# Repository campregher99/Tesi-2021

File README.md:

# Tesi-2021
progetto di tesi SCARA repository personale di backup

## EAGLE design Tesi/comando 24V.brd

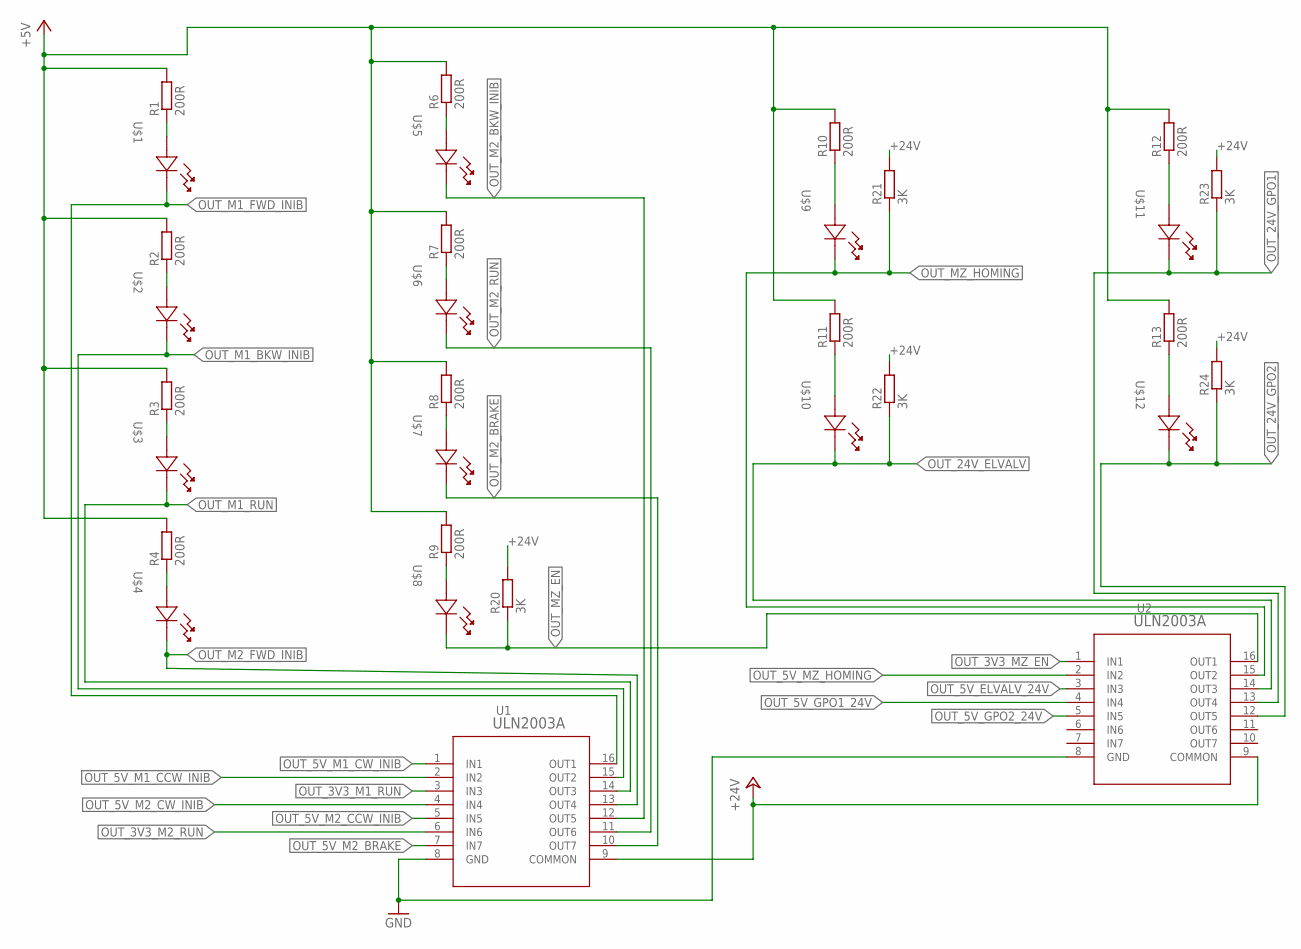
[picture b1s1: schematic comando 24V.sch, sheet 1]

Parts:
R1, R2, R3, R4, R6, R7, R8, R9, R10, R11, R12, R13: 200R; 0207/10
R20, R21, R22, R23, R24: 3K; 0207/10
U1, U2: ULN2003A; DIP-16_STM
U$1, U$2, U$3, U$4, U$5, U$6, U$7, U$8, U$9, U$10, U$11, U$12: LED_TONDO

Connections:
+5V: R1.2, R2.2, R3.2, R4.2, R6.2, R7.2, R8.2, R9.2, R10.2, R11.2, R12.2, R13.2; also elsewhere on the board
+24V: R20.2, R21.2, R22.2, R23.2, R24.2, U1.9 (COMMON), U2.9 (COMMON); also elsewhere on the board
GND: U1.8 (GND), U2.8 (GND); also elsewhere on the board
unnamed: R1.1, U$1.2
unnamed: R2.1, U$2.2
unnamed: R3.1, U$3.2
unnamed: R4.1, U$4.2
unnamed: R6.1, U$5.2
unnamed: R7.1, U$6.2
unnamed: R8.1, U$7.2
unnamed: R9.1, U$8.2
unnamed: R10.1, U$9.2
unnamed: R11.1, U$10.2
unnamed: R12.1, U$11.2
unnamed: R13.1, U$12.2
OUT_3V3_M1_RUN: U1.3 (IN3); also elsewhere on the board
OUT_3V3_M2_RUN: U1.6 (IN6); also elsewhere on the board
OUT_3V3_MZ_EN: U2.1 (IN1); also elsewhere on the board
OUT_5V_ELVALV_24V: U2.3 (IN3); also elsewhere on the board
OUT_5V_GPO1_24V: U2.4 (IN4); also elsewhere on the board
OUT_5V_GPO2_24V: U2.5 (IN5); also elsewhere on the board
OUT_5V_M1_CCW_INIB: U1.2 (IN2); also elsewhere on the board
OUT_5V_M1_CW_INIB: U1.1 (IN1); also elsewhere on the board
OUT_5V_M2_BRAKE: U1.7 (IN7); also elsewhere on the board
OUT_5V_M2_CCW_INIB: U1.5 (IN5); also elsewhere on the board
OUT_5V_M2_CW_INIB: U1.4 (IN4); also elsewhere on the board
OUT_5V_MZ_HOMING: U2.2 (IN2); also elsewhere on the board
OUT_24V_ELVALV: R22.1, U2.14 (OUT3), U$10.1; also elsewhere on the board
OUT_24V_GPO1: R23.1, U2.13 (OUT4), U$11.1; also elsewhere on the board
OUT_24V_GPO2: R24.1, U2.12 (OUT5), U$12.1; also elsewhere on the board
OUT_M1_BKW_INIB: U1.15 (OUT2), U$2.1; also elsewhere on the board
OUT_M1_FWD_INIB: U1.16 (OUT1), U$1.1; also elsewhere on the board
OUT_M1_RUN: U1.14 (OUT3), U$3.1; also elsewhere on the board
OUT_M2_BKW_INIB: U1.12 (OUT5), U$5.1; also elsewhere on the board
OUT_M2_BRAKE: U1.10 (OUT7), U$7.1; also elsewhere on the board
OUT_M2_FWD_INIB: U1.13 (OUT4), U$4.1; also elsewhere on the board
OUT_M2_RUN: U1.11 (OUT6), U$6.1; also elsewhere on the board
OUT_MZ_EN: R20.1, U2.16 (OUT1), U$8.1; also elsewhere on the board
OUT_MZ_HOMING: R21.1, U2.15 (OUT2), U$9.1; also elsewhere on the board

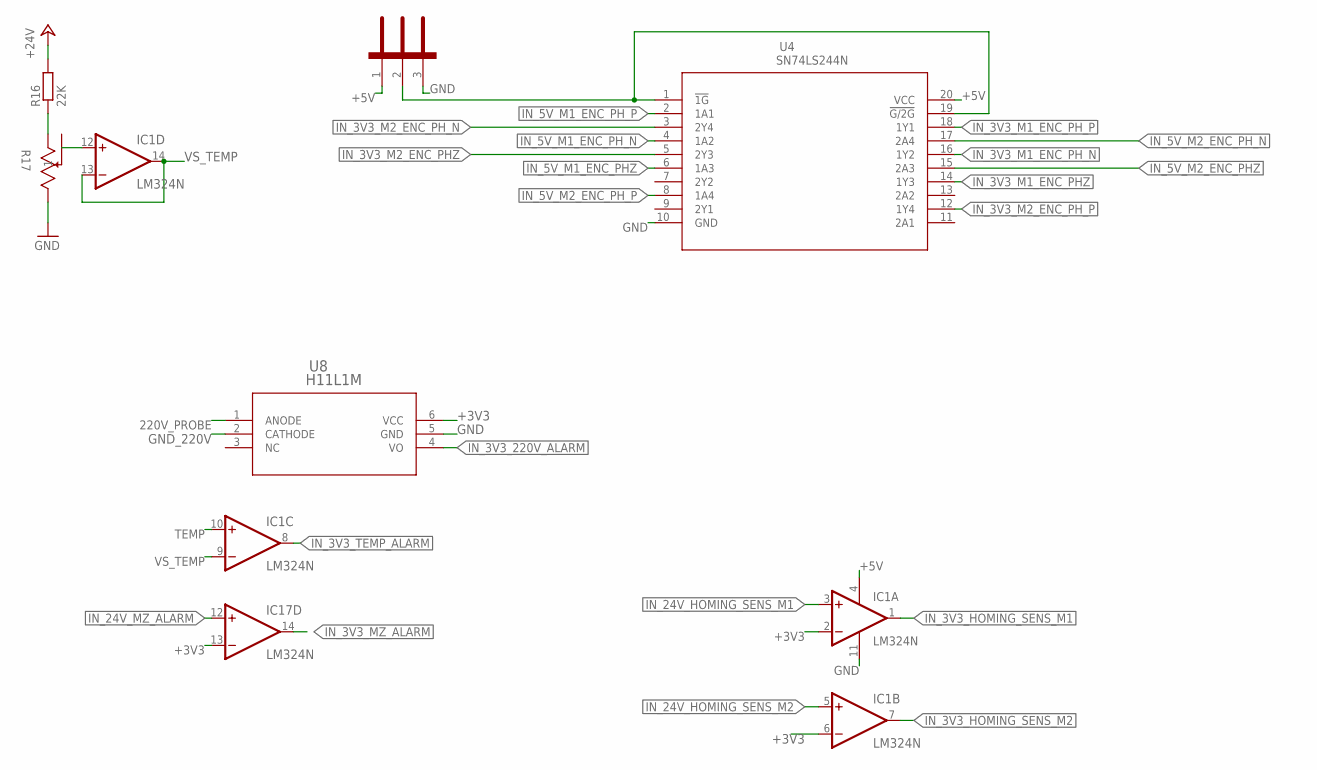
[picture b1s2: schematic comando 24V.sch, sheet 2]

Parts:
EN_IN_ENC: STRIP_3
IC1, IC17: LM324N; DIL14
R16: 22K; 0207/10
R17: TEMP_ADJ; RES3_64W_TTE
U4: SN74LS244N; N20
U8: H11L1M; PDIP6-646BX_ONS

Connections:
220V_PROBE: U8.1 (ANODE); also elsewhere on the board
+3V3: IC1.2 (-IN), IC1.6 (-IN), IC17.13 (-IN), U8.6 (VCC); also elsewhere on the board
+5V: EN_IN_ENC.1, IC1.4 (V+), U4.20 (VCC); also elsewhere on the board
+24V: R16.2; also elsewhere on the board
GND: EN_IN_ENC.3, IC1.11 (V-), R17.3, U4.10 (GND), U8.5 (GND); also elsewhere on the board
GND_220V: U8.2 (CATHODE); also elsewhere on the board
IN_3V3_220V_ALARM: U8.4 (VO); also elsewhere on the board
IN_3V3_HOMING_SENS_M1: IC1.1 (OUT); also elsewhere on the board
IN_3V3_HOMING_SENS_M2: IC1.7 (OUT); also elsewhere on the board
IN_3V3_M1_ENC_PHZ: U4.14 (1Y3); also elsewhere on the board
IN_3V3_M1_ENC_PH_N: U4.16 (1Y2); also elsewhere on the board
IN_3V3_M1_ENC_PH_P: U4.18 (1Y1); also elsewhere on the board
IN_3V3_M2_ENC_PHZ: U4.5 (2Y3); also elsewhere on the board
IN_3V3_M2_ENC_PH_N: U4.3 (2Y4); also elsewhere on the board
IN_3V3_M2_ENC_PH_P: U4.12 (1Y4); also elsewhere on the board
IN_3V3_MZ_ALARM: IC17.14 (OUT); also elsewhere on the board
IN_3V3_TEMP_ALARM: IC1.8 (OUT); also elsewhere on the board
IN_5V_M1_ENC_PHZ: U4.6 (1A3); also elsewhere on the board
IN_5V_M1_ENC_PH_N: U4.4 (1A2); also elsewhere on the board
IN_5V_M1_ENC_PH_P: U4.2 (1A1); also elsewhere on the board
IN_5V_M2_ENC_PHZ: U4.15 (2A3); also elsewhere on the board
IN_5V_M2_ENC_PH_N: U4.17 (2A4); also elsewhere on the board
IN_5V_M2_ENC_PH_P: U4.8 (1A4); also elsewhere on the board
IN_24V_HOMING_SENS_M1: IC1.3 (+IN); also elsewhere on the board
IN_24V_HOMING_SENS_M2: IC1.5 (+IN); also elsewhere on the board
IN_24V_MZ_ALARM: IC17.12 (+IN); also elsewhere on the board
unnamed: R16.1, R17.1
unnamed: IC1.12 (+IN), R17.2
unnamed: EN_IN_ENC.2, U4.1 (!1G), U4.19 (!G/2G)
TEMP: IC1.10 (+IN); also elsewhere on the board
VS_TEMP: IC1.9 (-IN), IC1.13 (-IN), IC1.14 (OUT)

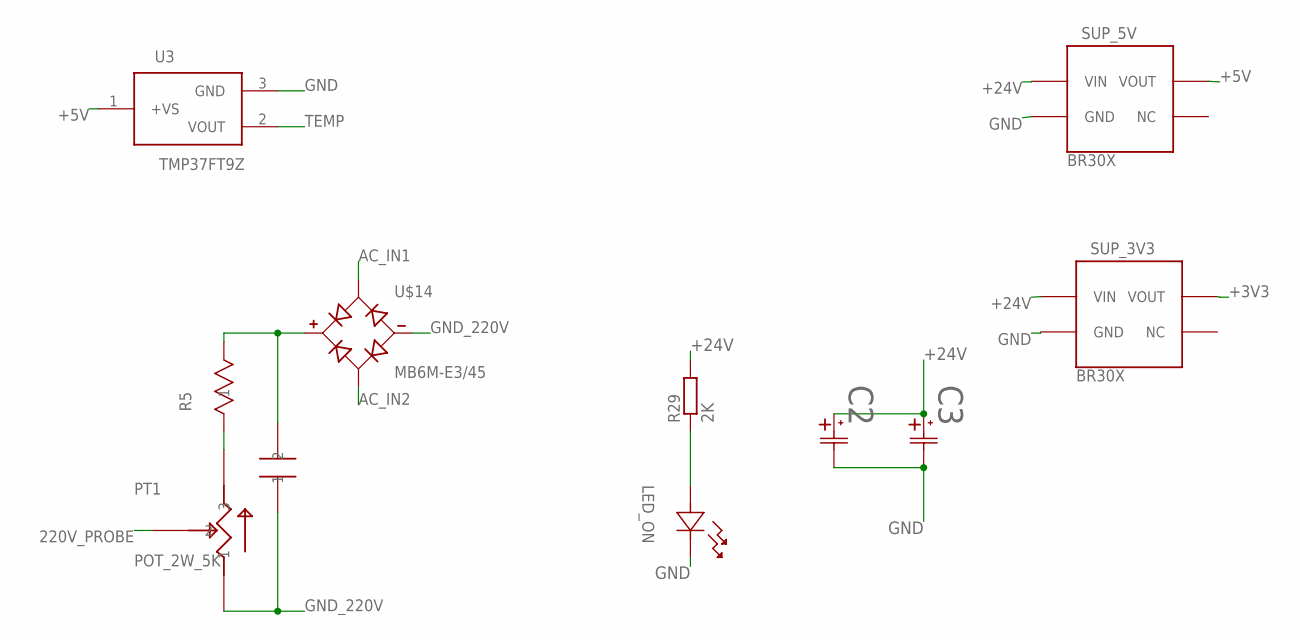
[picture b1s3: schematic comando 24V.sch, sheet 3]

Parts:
C2: QYX1H102JTP3TA; CAP_QYX_2P5X5X8P5_NCH
C3: UBY2A301MHL; CAP_UBY_12P5X31P5_NCH
PT1: POT_2W_5K
R5: OY104KE; RES_OY_OHM
R29: 2K; 0207/10
SUP_3V3, SUP_5V: BR30X
U3: TMP37FT9Z; T_3_ADI
U$13: C0U12F
U$14: MB6M-E3/45; DIP508W58P254L483H270Q4
U$15: LED_ON; LED_TONDO

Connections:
220V_PROBE: PT1.2; also elsewhere on the board
+3V3: SUP_3V3.VOUT; also elsewhere on the board
+5V: SUP_5V.VOUT, U3.1 (+VS); also elsewhere on the board
+24V: C2.1, C3.1, R29.2, SUP_3V3.VIN, SUP_5V.VIN; also elsewhere on the board
AC_IN1: U$14.3 (AC1); also elsewhere on the board
AC_IN2: U$14.4 (AC2); also elsewhere on the board
GND: C2.2, C3.2, SUP_3V3.GND, SUP_5V.GND, U3.3 (GND), U$15.1; also elsewhere on the board
GND_220V: PT1.1, U$13.P$2 (2), U$14.2 (-); also elsewhere on the board
unnamed: R5.2, U$13.P$1 (1), U$14.1 (+)
unnamed: R29.1, U$15.2
unnamed: PT1.3, R5.1
TEMP: U3.2 (VOUT); also elsewhere on the board

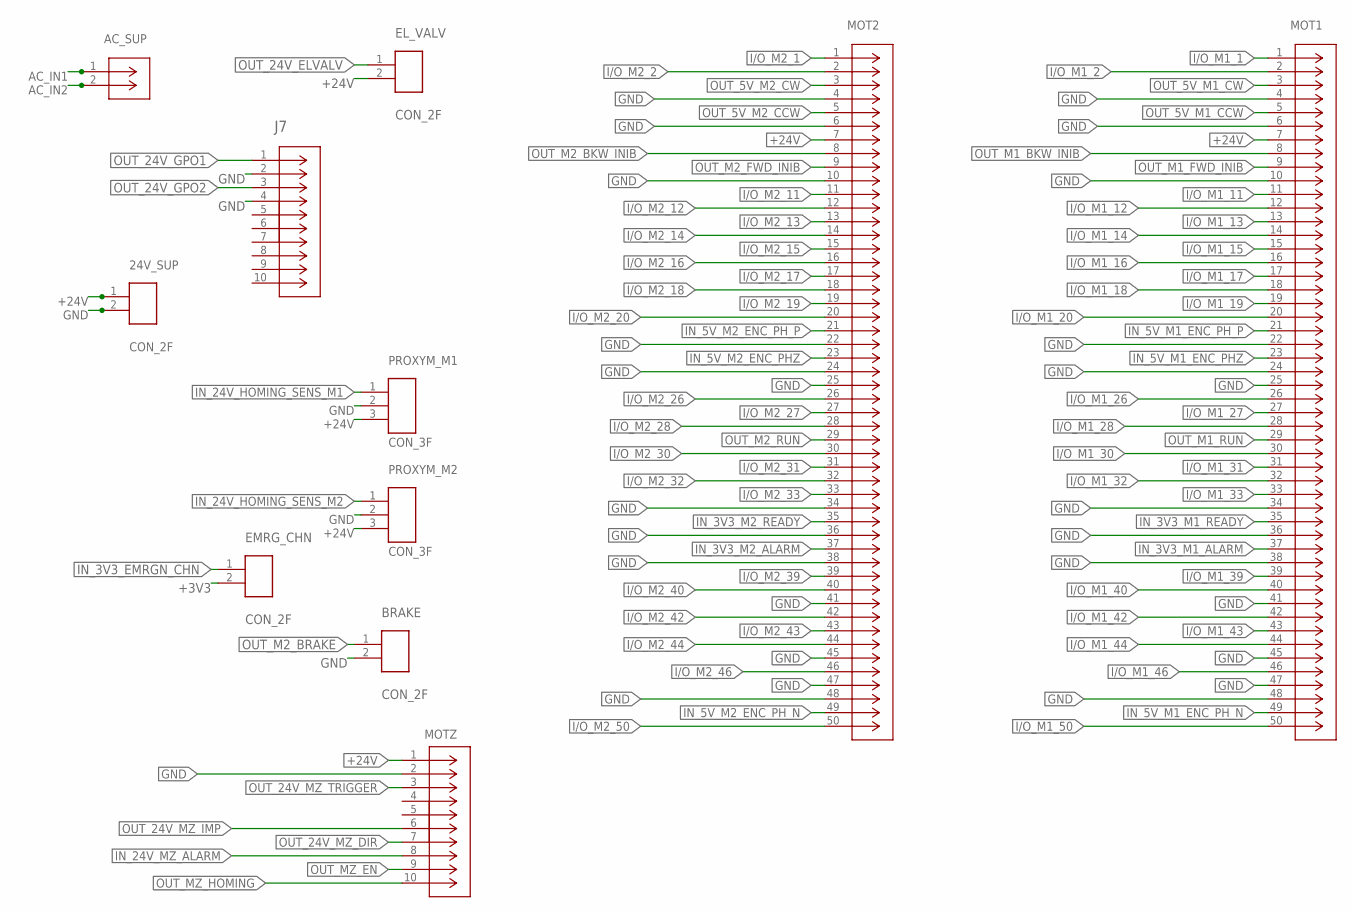
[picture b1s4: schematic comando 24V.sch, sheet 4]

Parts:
24V_SUP: CON_2F
AC_SUP: B2B-XH-A(LF)(SN); CONN_B2B-XH-A(LF)(SN)_JST
BRAKE: CON_2F
EL_VALV: CON_2F
EMRG_CHN: CON_2F
J7: 61201021621; CONN_61201021621_WRE
MOT1, MOT2: SBH11-PBPC-D25-ST-BK; CONN_SBH11-PBPC-D25-ST-BK_SUL
MOTZ: 61201021621; CONN_61201021621_WRE
PROXYM_M1, PROXYM_M2: CON_3F

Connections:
+3V3: EMRG_CHN.2; also elsewhere on the board
+24V: 24V_SUP.1, EL_VALV.2, MOT1.7, MOT2.7, MOTZ.1, PROXYM_M1.3, PROXYM_M2.3; also elsewhere on the board
AC_IN1: AC_SUP.1; also elsewhere on the board
AC_IN2: AC_SUP.2; also elsewhere on the board
GND: 24V_SUP.2, BRAKE.2, J7.2, J7.4, MOT1.4, MOT1.6, MOT1.10, MOT1.22, MOT1.24, MOT1.25, MOT1.34, MOT1.36, MOT1.38, MOT1.41, MOT1.45, MOT1.47, MOT1.48, MOT2.4, MOT2.6, MOT2.10, MOT2.22, MOT2.24, MOT2.25, MOT2.34, MOT2.36, MOT2.38, MOT2.41, MOT2.45, MOT2.47, MOT2.48, MOTZ.2, PROXYM_M1.2, PROXYM_M2.2; also elsewhere on the board
I/O_M1_1: MOT1.1; also elsewhere on the board
I/O_M1_2: MOT1.2; also elsewhere on the board
I/O_M1_11: MOT1.11; also elsewhere on the board
I/O_M1_12: MOT1.12; also elsewhere on the board
I/O_M1_13: MOT1.13; also elsewhere on the board
I/O_M1_14: MOT1.14; also elsewhere on the board
I/O_M1_15: MOT1.15; also elsewhere on the board
I/O_M1_16: MOT1.16; also elsewhere on the board
I/O_M1_17: MOT1.17; also elsewhere on the board
I/O_M1_18: MOT1.18; also elsewhere on the board
I/O_M1_19: MOT1.19; also elsewhere on the board
I/O_M1_20: MOT1.20; also elsewhere on the board
I/O_M1_26: MOT1.26; also elsewhere on the board
I/O_M1_27: MOT1.27; also elsewhere on the board
I/O_M1_28: MOT1.28; also elsewhere on the board
I/O_M1_30: MOT1.30; also elsewhere on the board
I/O_M1_31: MOT1.31; also elsewhere on the board
I/O_M1_32: MOT1.32; also elsewhere on the board
I/O_M1_33: MOT1.33; also elsewhere on the board
I/O_M1_39: MOT1.39; also elsewhere on the board
I/O_M1_40: MOT1.40; also elsewhere on the board
I/O_M1_42: MOT1.42; also elsewhere on the board
I/O_M1_43: MOT1.43; also elsewhere on the board
I/O_M1_44: MOT1.44; also elsewhere on the board
I/O_M1_46: MOT1.46; also elsewhere on the board
I/O_M1_50: MOT1.50; also elsewhere on the board
I/O_M2_1: MOT2.1; also elsewhere on the board
I/O_M2_2: MOT2.2; also elsewhere on the board
I/O_M2_11: MOT2.11; also elsewhere on the board
I/O_M2_12: MOT2.12; also elsewhere on the board
I/O_M2_13: MOT2.13; also elsewhere on the board
I/O_M2_14: MOT2.14; also elsewhere on the board
I/O_M2_15: MOT2.15; also elsewhere on the board
I/O_M2_16: MOT2.16; also elsewhere on the board
I/O_M2_17: MOT2.17; also elsewhere on the board
I/O_M2_18: MOT2.18; also elsewhere on the board
I/O_M2_19: MOT2.19; also elsewhere on the board
I/O_M2_20: MOT2.20; also elsewhere on the board
I/O_M2_26: MOT2.26; also elsewhere on the board
I/O_M2_27: MOT2.27; also elsewhere on the board
I/O_M2_28: MOT2.28; also elsewhere on the board
I/O_M2_30: MOT2.30; also elsewhere on the board
I/O_M2_31: MOT2.31; also elsewhere on the board
I/O_M2_32: MOT2.32; also elsewhere on the board
I/O_M2_33: MOT2.33; also elsewhere on the board
I/O_M2_39: MOT2.39; also elsewhere on the board
I/O_M2_40: MOT2.40; also elsewhere on the board
I/O_M2_42: MOT2.42; also elsewhere on the board
I/O_M2_43: MOT2.43; also elsewhere on the board
I/O_M2_44: MOT2.44; also elsewhere on the board
I/O_M2_46: MOT2.46; also elsewhere on the board
I/O_M2_50: MOT2.50; also elsewhere on the board
IN_3V3_EMRGN_CHN: EMRG_CHN.1; also elsewhere on the board
IN_3V3_M1_ALARM: MOT1.37; also elsewhere on the board
IN_3V3_M1_READY: MOT1.35; also elsewhere on the board
IN_3V3_M2_ALARM: MOT2.37; also elsewhere on the board
IN_3V3_M2_READY: MOT2.35; also elsewhere on the board
IN_5V_M1_ENC_PHZ: MOT1.23; also elsewhere on the board
IN_5V_M1_ENC_PH_N: MOT1.49; also elsewhere on the board
IN_5V_M1_ENC_PH_P: MOT1.21; also elsewhere on the board
IN_5V_M2_ENC_PHZ: MOT2.23; also elsewhere on the board
IN_5V_M2_ENC_PH_N: MOT2.49; also elsewhere on the board
IN_5V_M2_ENC_PH_P: MOT2.21; also elsewhere on the board
IN_24V_HOMING_SENS_M1: PROXYM_M1.1; also elsewhere on the board
IN_24V_HOMING_SENS_M2: PROXYM_M2.1; also elsewhere on the board
IN_24V_MZ_ALARM: MOTZ.8; also elsewhere on the board
OUT_5V_M1_CCW: MOT1.5; also elsewhere on the board
OUT_5V_M1_CW: MOT1.3; also elsewhere on the board
OUT_5V_M2_CCW: MOT2.5; also elsewhere on the board
OUT_5V_M2_CW: MOT2.3; also elsewhere on the board
OUT_24V_ELVALV: EL_VALV.1; also elsewhere on the board
OUT_24V_GPO1: J7.1; also elsewhere on the board
OUT_24V_GPO2: J7.3; also elsewhere on the board
OUT_24V_MZ_DIR: MOTZ.7; also elsewhere on the board
OUT_24V_MZ_IMP: MOTZ.6; also elsewhere on the board
OUT_24V_MZ_TRIGGER: MOTZ.3; also elsewhere on the board
OUT_M1_BKW_INIB: MOT1.8; also elsewhere on the board
OUT_M1_FWD_INIB: MOT1.9; also elsewhere on the board
OUT_M1_RUN: MOT1.29; also elsewhere on the board
OUT_M2_BKW_INIB: MOT2.8; also elsewhere on the board
OUT_M2_BRAKE: BRAKE.1; also elsewhere on the board
OUT_M2_FWD_INIB: MOT2.9; also elsewhere on the board
OUT_M2_RUN: MOT2.29; also elsewhere on the board
OUT_MZ_EN: MOTZ.9; also elsewhere on the board
OUT_MZ_HOMING: MOTZ.10; also elsewhere on the board

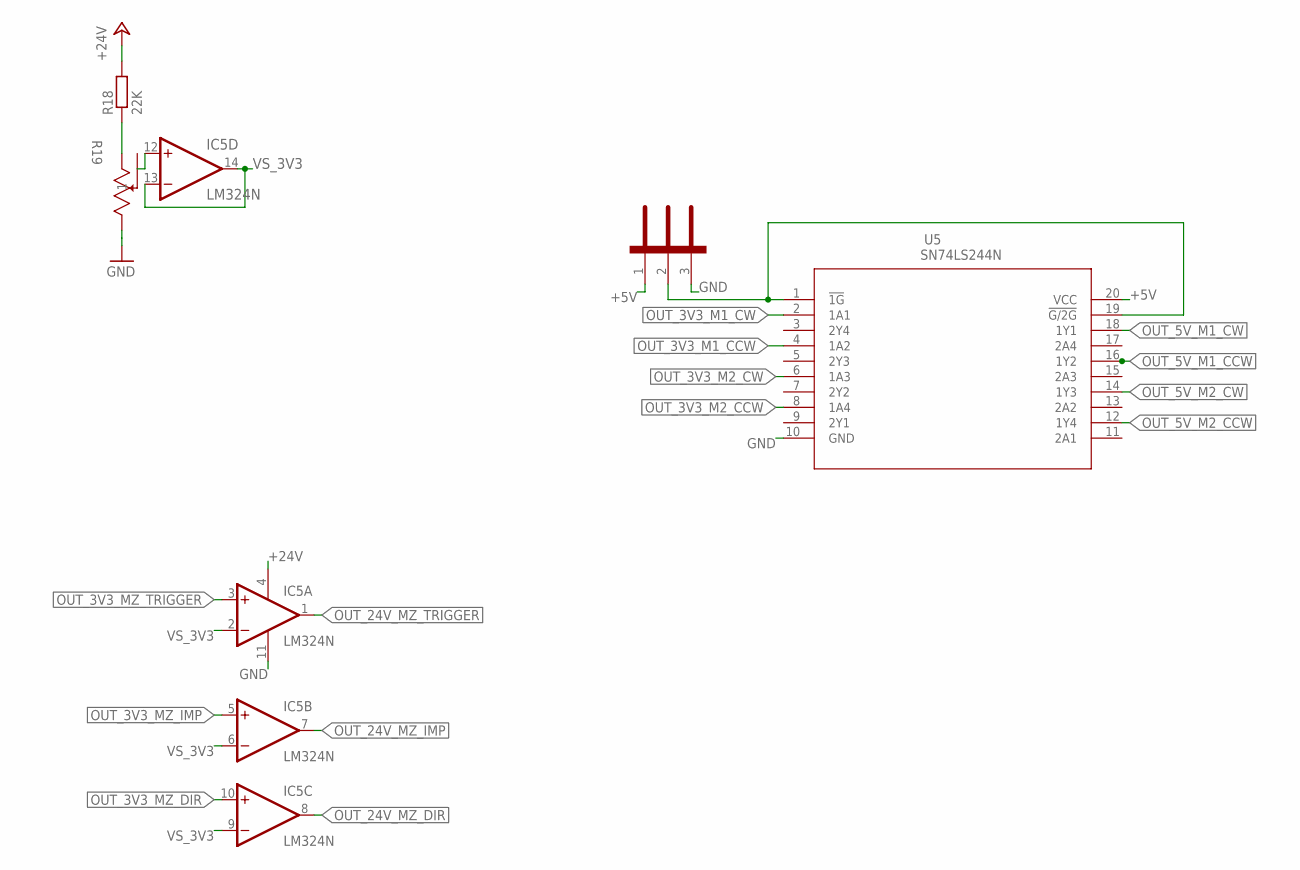
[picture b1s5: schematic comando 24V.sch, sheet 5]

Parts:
EN_OUT_MOT: STRIP_3
IC5: LM324N; DIL14
R18: 22K; 0207/10
R19: VS_3V3_ADJ; RES3_64W_TTE
U5: SN74LS244N; N20

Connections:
+5V: EN_OUT_MOT.1, U5.20 (VCC); also elsewhere on the board
+24V: IC5.4 (V+), R18.2; also elsewhere on the board
GND: EN_OUT_MOT.3, IC5.11 (V-), R19.3, U5.10 (GND); also elsewhere on the board
unnamed: EN_OUT_MOT.2, U5.1 (!1G), U5.19 (!G/2G)
unnamed: IC5.12 (+IN), R19.2
unnamed: R18.1, R19.1
OUT_3V3_M1_CCW: U5.4 (1A2); also elsewhere on the board
OUT_3V3_M1_CW: U5.2 (1A1); also elsewhere on the board
OUT_3V3_M2_CCW: U5.8 (1A4); also elsewhere on the board
OUT_3V3_M2_CW: U5.6 (1A3); also elsewhere on the board
OUT_3V3_MZ_DIR: IC5.10 (+IN); also elsewhere on the board
OUT_3V3_MZ_IMP: IC5.5 (+IN); also elsewhere on the board
OUT_3V3_MZ_TRIGGER: IC5.3 (+IN); also elsewhere on the board
OUT_5V_M1_CCW: U5.16 (1Y2); also elsewhere on the board
OUT_5V_M1_CW: U5.18 (1Y1); also elsewhere on the board
OUT_5V_M2_CCW: U5.12 (1Y4); also elsewhere on the board
OUT_5V_M2_CW: U5.14 (1Y3); also elsewhere on the board
OUT_24V_MZ_DIR: IC5.8 (OUT); also elsewhere on the board
OUT_24V_MZ_IMP: IC5.7 (OUT); also elsewhere on the board
OUT_24V_MZ_TRIGGER: IC5.1 (OUT); also elsewhere on the board
VS_3V3: IC5.2 (-IN), IC5.6 (-IN), IC5.9 (-IN), IC5.13 (-IN), IC5.14 (OUT)

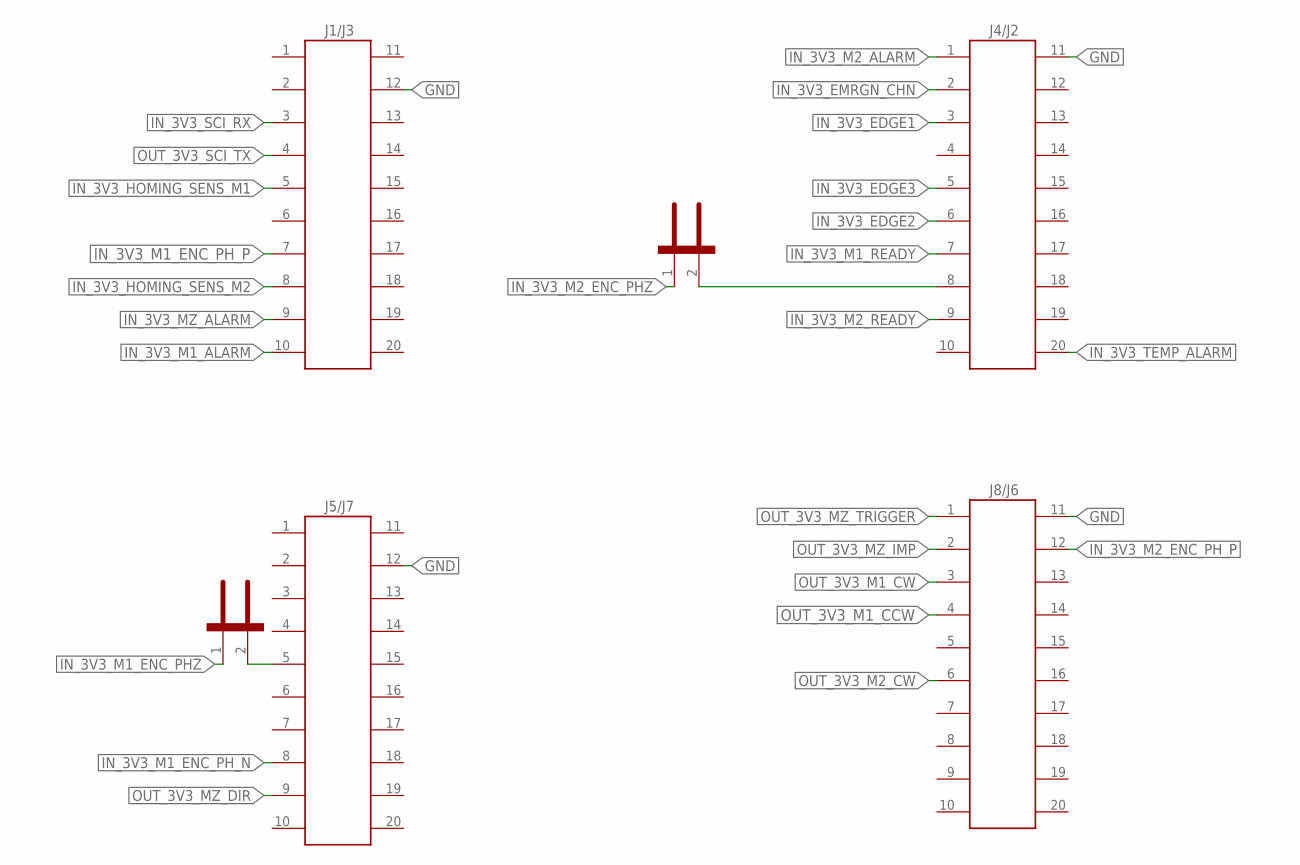
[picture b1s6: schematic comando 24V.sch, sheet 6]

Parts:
EN_M1_ENC_PHZ, EN_M2_ENC_PHZ: STRIP_2
J1/J3, J4/J2, J5/J7, J8/J6: 61202021621

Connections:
GND: J1/J3.12 (4), J4/J2.11 (2), J5/J7.12 (4), J8/J6.11 (2); also elsewhere on the board
IN_3V3_EDGE1: J4/J2.3 (5); also elsewhere on the board
IN_3V3_EDGE2: J4/J2.6 (11); also elsewhere on the board
IN_3V3_EDGE3: J4/J2.5 (9); also elsewhere on the board
IN_3V3_EMRGN_CHN: J4/J2.2 (3); also elsewhere on the board
IN_3V3_HOMING_SENS_M1: J1/J3.5 (9); also elsewhere on the board
IN_3V3_HOMING_SENS_M2: J1/J3.8 (15); also elsewhere on the board
IN_3V3_M1_ALARM: J1/J3.10 (19); also elsewhere on the board
IN_3V3_M1_ENC_PHZ: EN_M1_ENC_PHZ.1; also elsewhere on the board
IN_3V3_M1_ENC_PH_N: J5/J7.8 (15); also elsewhere on the board
IN_3V3_M1_ENC_PH_P: J1/J3.7 (13); also elsewhere on the board
IN_3V3_M1_READY: J4/J2.7 (13); also elsewhere on the board
IN_3V3_M2_ALARM: J4/J2.1; also elsewhere on the board
IN_3V3_M2_ENC_PHZ: EN_M2_ENC_PHZ.1; also elsewhere on the board
IN_3V3_M2_ENC_PH_P: J8/J6.12 (4); also elsewhere on the board
IN_3V3_M2_READY: J4/J2.9 (17); also elsewhere on the board
IN_3V3_MZ_ALARM: J1/J3.9 (17); also elsewhere on the board
IN_3V3_SCI_RX: J1/J3.3 (5); also elsewhere on the board
IN_3V3_TEMP_ALARM: J4/J2.20; also elsewhere on the board
unnamed: EN_M2_ENC_PHZ.2, J4/J2.8 (15)
unnamed: EN_M1_ENC_PHZ.2, J5/J7.5 (9)
OUT_3V3_M1_CCW: J8/J6.4 (7); also elsewhere on the board
OUT_3V3_M1_CW: J8/J6.3 (5); also elsewhere on the board
OUT_3V3_M2_CW: J8/J6.6 (11); also elsewhere on the board
OUT_3V3_MZ_DIR: J5/J7.9 (17); also elsewhere on the board
OUT_3V3_MZ_IMP: J8/J6.2 (3); also elsewhere on the board
OUT_3V3_MZ_TRIGGER: J8/J6.1; also elsewhere on the board
OUT_3V3_SCI_TX: J1/J3.4 (7); also elsewhere on the board

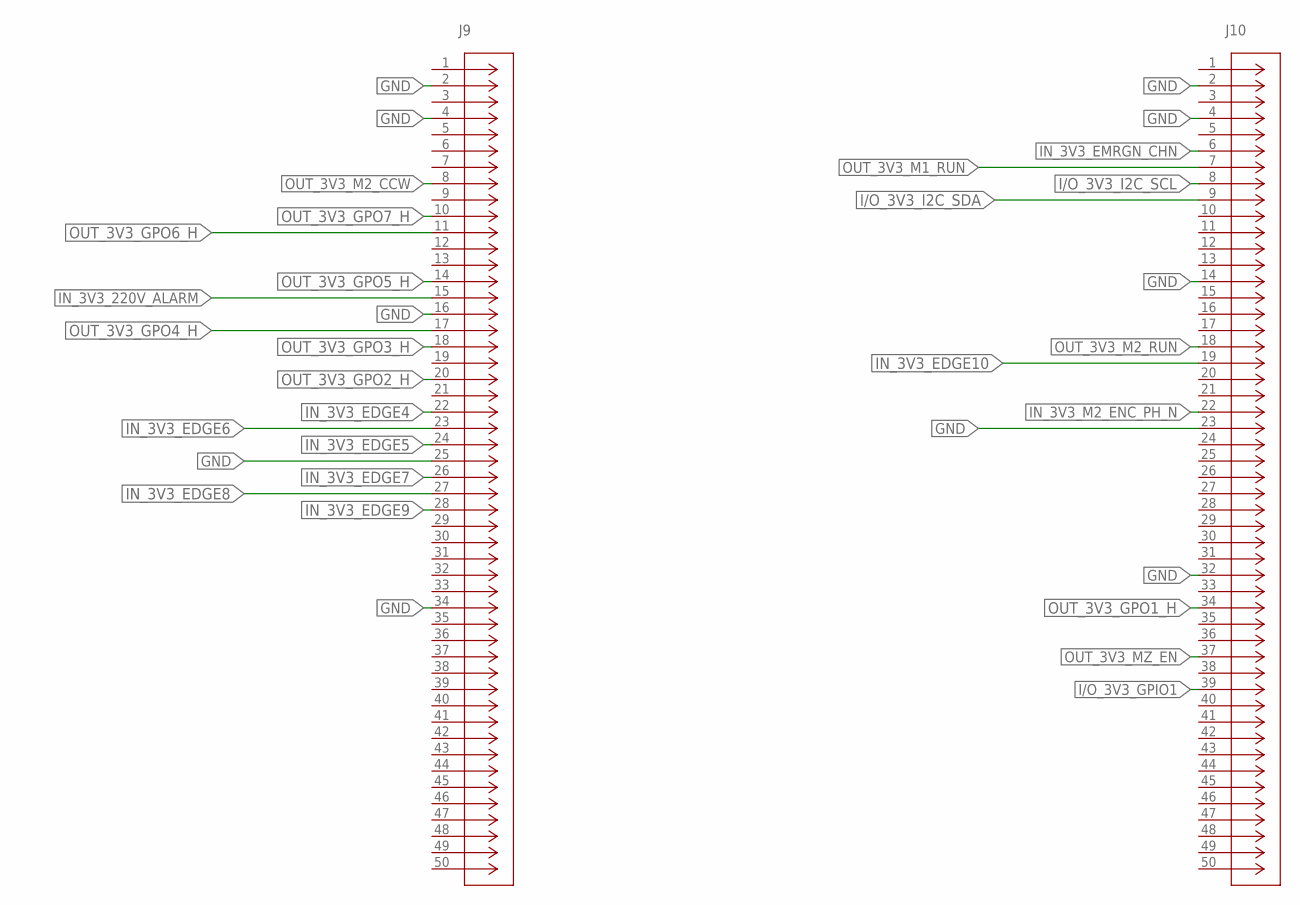
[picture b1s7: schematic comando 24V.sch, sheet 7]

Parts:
J9, J10: SBH11-PBPC-D25-ST-BK; CONN_SBH11-PBPC-D25-ST-BK_SUL

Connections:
GND: J9.2, J9.4, J9.16, J9.25, J9.34, J10.2, J10.4, J10.14, J10.23, J10.32; also elsewhere on the board
I/O_3V3_GPIO1: J10.39; also elsewhere on the board
I/O_3V3_I2C_SCL: J10.8; also elsewhere on the board
I/O_3V3_I2C_SDA: J10.9; also elsewhere on the board
IN_3V3_220V_ALARM: J9.15; also elsewhere on the board
IN_3V3_EDGE4: J9.22; also elsewhere on the board
IN_3V3_EDGE5: J9.24; also elsewhere on the board
IN_3V3_EDGE6: J9.23; also elsewhere on the board
IN_3V3_EDGE7: J9.26; also elsewhere on the board
IN_3V3_EDGE8: J9.27; also elsewhere on the board
IN_3V3_EDGE9: J9.28; also elsewhere on the board
IN_3V3_EDGE10: J10.19; also elsewhere on the board
IN_3V3_EMRGN_CHN: J10.6; also elsewhere on the board
IN_3V3_M2_ENC_PH_N: J10.22; also elsewhere on the board
OUT_3V3_GPO1_H: J10.34; also elsewhere on the board
OUT_3V3_GPO2_H: J9.20; also elsewhere on the board
OUT_3V3_GPO3_H: J9.18; also elsewhere on the board
OUT_3V3_GPO4_H: J9.17; also elsewhere on the board
OUT_3V3_GPO5_H: J9.14; also elsewhere on the board
OUT_3V3_GPO6_H: J9.11; also elsewhere on the board
OUT_3V3_GPO7_H: J9.10; also elsewhere on the board
OUT_3V3_M1_RUN: J10.7; also elsewhere on the board
OUT_3V3_M2_CCW: J9.8; also elsewhere on the board
OUT_3V3_M2_RUN: J10.18; also elsewhere on the board
OUT_3V3_MZ_EN: J10.37; also elsewhere on the board

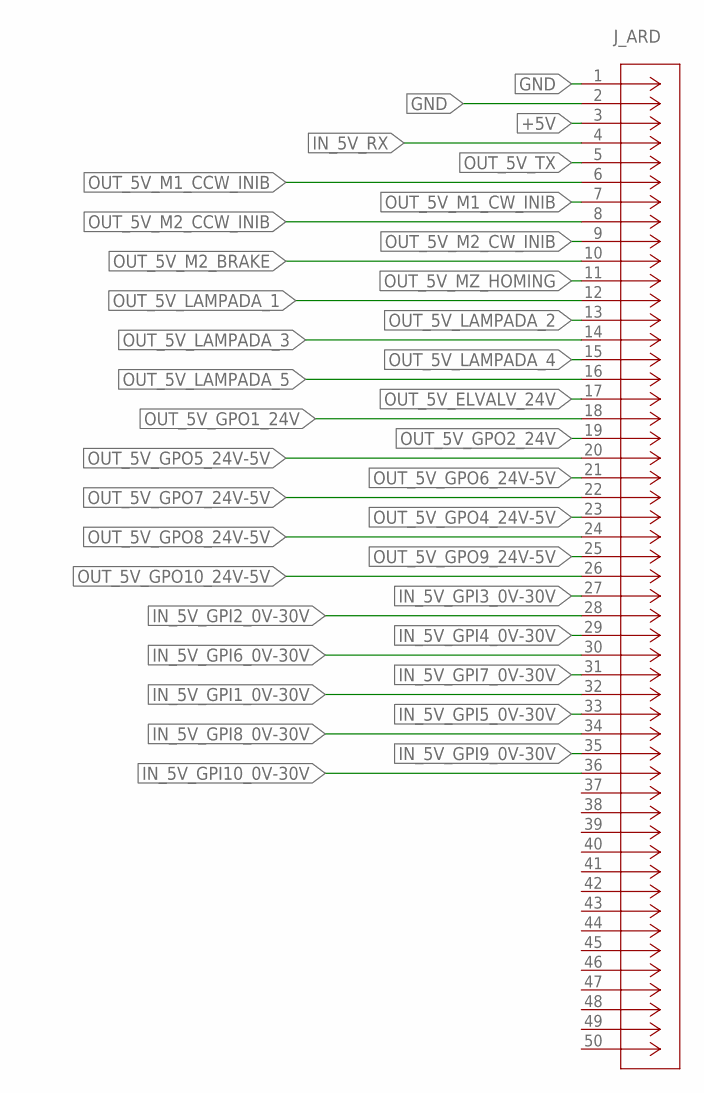
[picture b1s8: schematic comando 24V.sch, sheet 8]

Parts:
J_ARD: SBH11-PBPC-D25-ST-BK; CONN_SBH11-PBPC-D25-ST-BK_SUL

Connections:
+5V: J_ARD.3; also elsewhere on the board
GND: J_ARD.1, J_ARD.2; also elsewhere on the board
IN_5V_GPI1_0V-30V: J_ARD.32; also elsewhere on the board
IN_5V_GPI2_0V-30V: J_ARD.28; also elsewhere on the board
IN_5V_GPI3_0V-30V: J_ARD.27; also elsewhere on the board
IN_5V_GPI4_0V-30V: J_ARD.29; also elsewhere on the board
IN_5V_GPI5_0V-30V: J_ARD.33; also elsewhere on the board
IN_5V_GPI6_0V-30V: J_ARD.30; also elsewhere on the board
IN_5V_GPI7_0V-30V: J_ARD.31; also elsewhere on the board
IN_5V_GPI8_0V-30V: J_ARD.34; also elsewhere on the board
IN_5V_GPI9_0V-30V: J_ARD.35; also elsewhere on the board
IN_5V_GPI10_0V-30V: J_ARD.36; also elsewhere on the board
IN_5V_RX: J_ARD.4; also elsewhere on the board
OUT_5V_ELVALV_24V: J_ARD.17; also elsewhere on the board
OUT_5V_GPO1_24V: J_ARD.18; also elsewhere on the board
OUT_5V_GPO2_24V: J_ARD.19; also elsewhere on the board
OUT_5V_GPO4_24V-5V: J_ARD.23; also elsewhere on the board
OUT_5V_GPO5_24V-5V: J_ARD.20; also elsewhere on the board
OUT_5V_GPO6_24V-5V: J_ARD.21; also elsewhere on the board
OUT_5V_GPO7_24V-5V: J_ARD.22; also elsewhere on the board
OUT_5V_GPO8_24V-5V: J_ARD.24; also elsewhere on the board
OUT_5V_GPO9_24V-5V: J_ARD.25; also elsewhere on the board
OUT_5V_GPO10_24V-5V: J_ARD.26; also elsewhere on the board
OUT_5V_LAMPADA_1: J_ARD.12; also elsewhere on the board
OUT_5V_LAMPADA_2: J_ARD.13; also elsewhere on the board
OUT_5V_LAMPADA_3: J_ARD.14; also elsewhere on the board
OUT_5V_LAMPADA_4: J_ARD.15; also elsewhere on the board
OUT_5V_LAMPADA_5: J_ARD.16; also elsewhere on the board
OUT_5V_M1_CCW_INIB: J_ARD.6; also elsewhere on the board
OUT_5V_M1_CW_INIB: J_ARD.7; also elsewhere on the board
OUT_5V_M2_BRAKE: J_ARD.10; also elsewhere on the board
OUT_5V_M2_CCW_INIB: J_ARD.8; also elsewhere on the board
OUT_5V_M2_CW_INIB: J_ARD.9; also elsewhere on the board
OUT_5V_MZ_HOMING: J_ARD.11; also elsewhere on the board
OUT_5V_TX: J_ARD.5; also elsewhere on the board

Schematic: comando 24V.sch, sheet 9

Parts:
EN_SCI: STRIP_3
IC7, IC11: LM324N; DIL14
J8: 61202021621
J_LAMPADE: 61201021621; CONN_61201021621_WRE
OUT_ARD_4-7_5V-24V, OUT_ARD_8-11_5V-24V: STRIP_3
R14: 22K; 0207/10
R15: VS_5v_ADJ; RES3_64W_TTE
U6: SN74LS244N; N20

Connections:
+5V: EN_SCI.1, OUT_ARD_4-7_5V-24V.1, OUT_ARD_8-11_5V-24V.1, U6.20 (VCC); also elsewhere on the board
+24V: OUT_ARD_4-7_5V-24V.3, OUT_ARD_8-11_5V-24V.3, R14.2; also elsewhere on the board
GND: EN_SCI.3, IC7.11 (V-), IC11.11 (V-), J8.1, J8.2 (3), J8.3 (5), J8.4 (7), J8.5 (9), J8.6 (11), J8.7 (13), J8.8 (15), J8.9 (17), J8.10 (19), J_LAMPADE.2, J_LAMPADE.4, J_LAMPADE.6, J_LAMPADE.8, J_LAMPADE.10, R15.3, U6.10 (GND); also elsewhere on the board
IN_3V3_SCI_RX: U6.3 (2Y4); also elsewhere on the board
IN_5V_RX: U6.18 (1Y1); also elsewhere on the board
unnamed: EN_SCI.2, U6.1 (!1G), U6.19 (!G/2G)
unnamed: R14.1, R15.1
unnamed: IC11.4 (V+), OUT_ARD_4-7_5V-24V.2
unnamed: IC7.4 (V+), OUT_ARD_8-11_5V-24V.2
unnamed: IC7.12 (+IN), R15.2
OUT_3V3_SCI_TX: U6.2 (1A1); also elsewhere on the board
OUT_5V_GPO4_24V-5V: IC11.12 (+IN); also elsewhere on the board
OUT_5V_GPO5_24V-5V: IC11.3 (+IN); also elsewhere on the board
OUT_5V_GPO6_24V-5V: IC11.5 (+IN); also elsewhere on the board
OUT_5V_GPO7_24V-5V: IC11.10 (+IN); also elsewhere on the board
OUT_5V_GPO8_24V-5V: IC7.3 (+IN); also elsewhere on the board
OUT_5V_GPO9_24V-5V: IC7.5 (+IN); also elsewhere on the board
OUT_5V_GPO10_24V-5V: IC7.10 (+IN); also elsewhere on the board
OUT_5V_LAMPADA_1: J_LAMPADE.1; also elsewhere on the board
OUT_5V_LAMPADA_2: J_LAMPADE.3; also elsewhere on the board
OUT_5V_LAMPADA_3: J_LAMPADE.5; also elsewhere on the board
OUT_5V_LAMPADA_4: J_LAMPADE.7; also elsewhere on the board
OUT_5V_LAMPADA_5: J_LAMPADE.9; also elsewhere on the board
OUT_5V_TX: U6.17 (2A4); also elsewhere on the board
OUT_24V-5V_GPO4: IC11.14 (OUT), J8.11 (2)
OUT_24V-5V_GPO5: IC11.1 (OUT), J8.12 (4)
OUT_24V-5V_GPO6: IC11.7 (OUT), J8.13 (6)
OUT_24V-5V_GPO7: IC11.8 (OUT), J8.14 (8)
OUT_24V-5V_GPO8: IC7.1 (OUT), J8.15 (10)
OUT_24V-5V_GPO9: IC7.7 (OUT), J8.16 (12)
OUT_24V-5V_GPO10: IC7.8 (OUT), J8.17 (14)
VS_5V: IC7.2 (-IN), IC7.6 (-IN), IC7.9 (-IN), IC7.13 (-IN), IC7.14 (OUT), IC11.2 (-IN), IC11.6 (-IN), IC11.9 (-IN), IC11.13 (-IN)

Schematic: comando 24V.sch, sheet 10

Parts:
IC12, IC13, IC14: LM324N; DIL14
JI_ARD: 61202021621
R25: 22K; 0207/10
R26: VS_ARD_ADJ; RES3_64W_TTE

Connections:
+5V: IC12.4 (V+), IC13.4 (V+), IC14.4 (V+); also elsewhere on the board
+24V: R25.2; also elsewhere on the board
GND: IC12.11 (V-), IC13.11 (V-), IC14.11 (V-), JI_ARD.1, JI_ARD.2 (3), JI_ARD.3 (5), JI_ARD.4 (7), JI_ARD.5 (9), JI_ARD.6 (11), JI_ARD.7 (13), JI_ARD.8 (15), JI_ARD.9 (17), JI_ARD.10 (19), R26.3; also elsewhere on the board
IN_5V_GPI1_0V-30V: IC12.14 (OUT); also elsewhere on the board
IN_5V_GPI2_0V-30V: IC12.8 (OUT); also elsewhere on the board
IN_5V_GPI3_0V-30V: IC12.7 (OUT); also elsewhere on the board
IN_5V_GPI4_0V-30V: IC13.1 (OUT); also elsewhere on the board
IN_5V_GPI5_0V-30V: IC13.7 (OUT); also elsewhere on the board
IN_5V_GPI6_0V-30V: IC13.8 (OUT); also elsewhere on the board
IN_5V_GPI7_0V-30V: IC13.14 (OUT); also elsewhere on the board
IN_5V_GPI8_0V-30V: IC14.1 (OUT); also elsewhere on the board
IN_5V_GPI9_0V-30V: IC14.7 (OUT); also elsewhere on the board
IN_5V_GPI10_0V-30V: IC14.8 (OUT); also elsewhere on the board
IN_30V_GPI1: IC12.12 (+IN), JI_ARD.11 (2)
IN_30V_GPI2: IC12.10 (+IN), JI_ARD.12 (4)
IN_30V_GPI3: IC12.5 (+IN), JI_ARD.13 (6)
IN_30V_GPI4: IC13.3 (+IN), JI_ARD.14 (8)
IN_30V_GPI5: IC13.5 (+IN), JI_ARD.15 (10)
IN_30V_GPI6: IC13.10 (+IN), JI_ARD.16 (12)
IN_30V_GPI7: IC13.12 (+IN), JI_ARD.17 (14)
IN_30V_GPI8: IC14.3 (+IN), JI_ARD.18 (16)
IN_30V_GPI9: IC14.5 (+IN), JI_ARD.19 (18)
IN_30V_GPI10: IC14.10 (+IN), JI_ARD.20
unnamed: R25.1, R26.1
unnamed: IC12.3 (+IN), R26.2
VS_IN_ARD: IC12.1 (OUT), IC12.2 (-IN), IC12.6 (-IN), IC12.9 (-IN), IC12.13 (-IN), IC13.2 (-IN), IC13.6 (-IN), IC13.9 (-IN), IC13.13 (-IN), IC14.2 (-IN), IC14.6 (-IN), IC14.9 (-IN)

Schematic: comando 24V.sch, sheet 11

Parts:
IC15, IC16, IC17: LM324N; DIL14
JI_TEXAS: 61202021621
R27: 22K; 0207/10
R28: VS_EDGE_ADJ; RES3_64W_TTE

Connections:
+5V: IC15.4 (V+), IC16.4 (V+), IC17.4 (V+); also elsewhere on the board
+24V: R27.2; also elsewhere on the board
GND: IC15.11 (V-), IC16.11 (V-), IC17.11 (V-), JI_TEXAS.1, JI_TEXAS.2 (3), JI_TEXAS.3 (5), JI_TEXAS.4 (7), JI_TEXAS.5 (9), JI_TEXAS.6 (11), JI_TEXAS.7 (13), JI_TEXAS.8 (15), JI_TEXAS.9 (17), JI_TEXAS.10 (19), R28.3; also elsewhere on the board
IN_3V3_EDGE1: IC15.14 (OUT); also elsewhere on the board
IN_3V3_EDGE2: IC15.8 (OUT); also elsewhere on the board
IN_3V3_EDGE3: IC15.7 (OUT); also elsewhere on the board
IN_3V3_EDGE4: IC17.1 (OUT); also elsewhere on the board
IN_3V3_EDGE5: IC17.7 (OUT); also elsewhere on the board
IN_3V3_EDGE6: IC17.8 (OUT); also elsewhere on the board
IN_3V3_EDGE7: IC16.1 (OUT); also elsewhere on the board
IN_3V3_EDGE8: IC16.7 (OUT); also elsewhere on the board
IN_3V3_EDGE9: IC16.14 (OUT); also elsewhere on the board
IN_3V3_EDGE10: IC16.8 (OUT); also elsewhere on the board
IN_30V_EDGE1: IC15.12 (+IN), JI_TEXAS.11 (2)
IN_30V_EDGE2: IC15.10 (+IN), JI_TEXAS.12 (4)
IN_30V_EDGE3: IC15.5 (+IN), JI_TEXAS.13 (6)
IN_30V_EDGE4: IC17.3 (+IN), JI_TEXAS.14 (8)
IN_30V_EDGE5: IC17.5 (+IN), JI_TEXAS.15 (10)
IN_30V_EDGE6: IC17.10 (+IN), JI_TEXAS.16 (12)
IN_30V_EDGE7: IC16.3 (+IN), JI_TEXAS.17 (14)
IN_30V_EDGE8: IC16.5 (+IN), JI_TEXAS.18 (16)
IN_30V_EDGE9: IC16.12 (+IN), JI_TEXAS.19 (18)
IN_30V_EDGE10: IC16.10 (+IN), JI_TEXAS.20
unnamed: R27.1, R28.1
unnamed: IC15.3 (+IN), R28.2
VS_IN_EDGE: IC15.1 (OUT), IC15.2 (-IN), IC15.6 (-IN), IC15.9 (-IN), IC15.13 (-IN), IC16.2 (-IN), IC16.6 (-IN), IC16.9 (-IN), IC16.13 (-IN), IC17.2 (-IN), IC17.6 (-IN), IC17.9 (-IN)

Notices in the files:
parts and their libraries:
COPYRIGHT: Copyright (C) 2018 Accelerated Designs. All rights reserved
COPYRIGHT: Copyright (C) 2016 Accelerated Designs. All rights reserved
